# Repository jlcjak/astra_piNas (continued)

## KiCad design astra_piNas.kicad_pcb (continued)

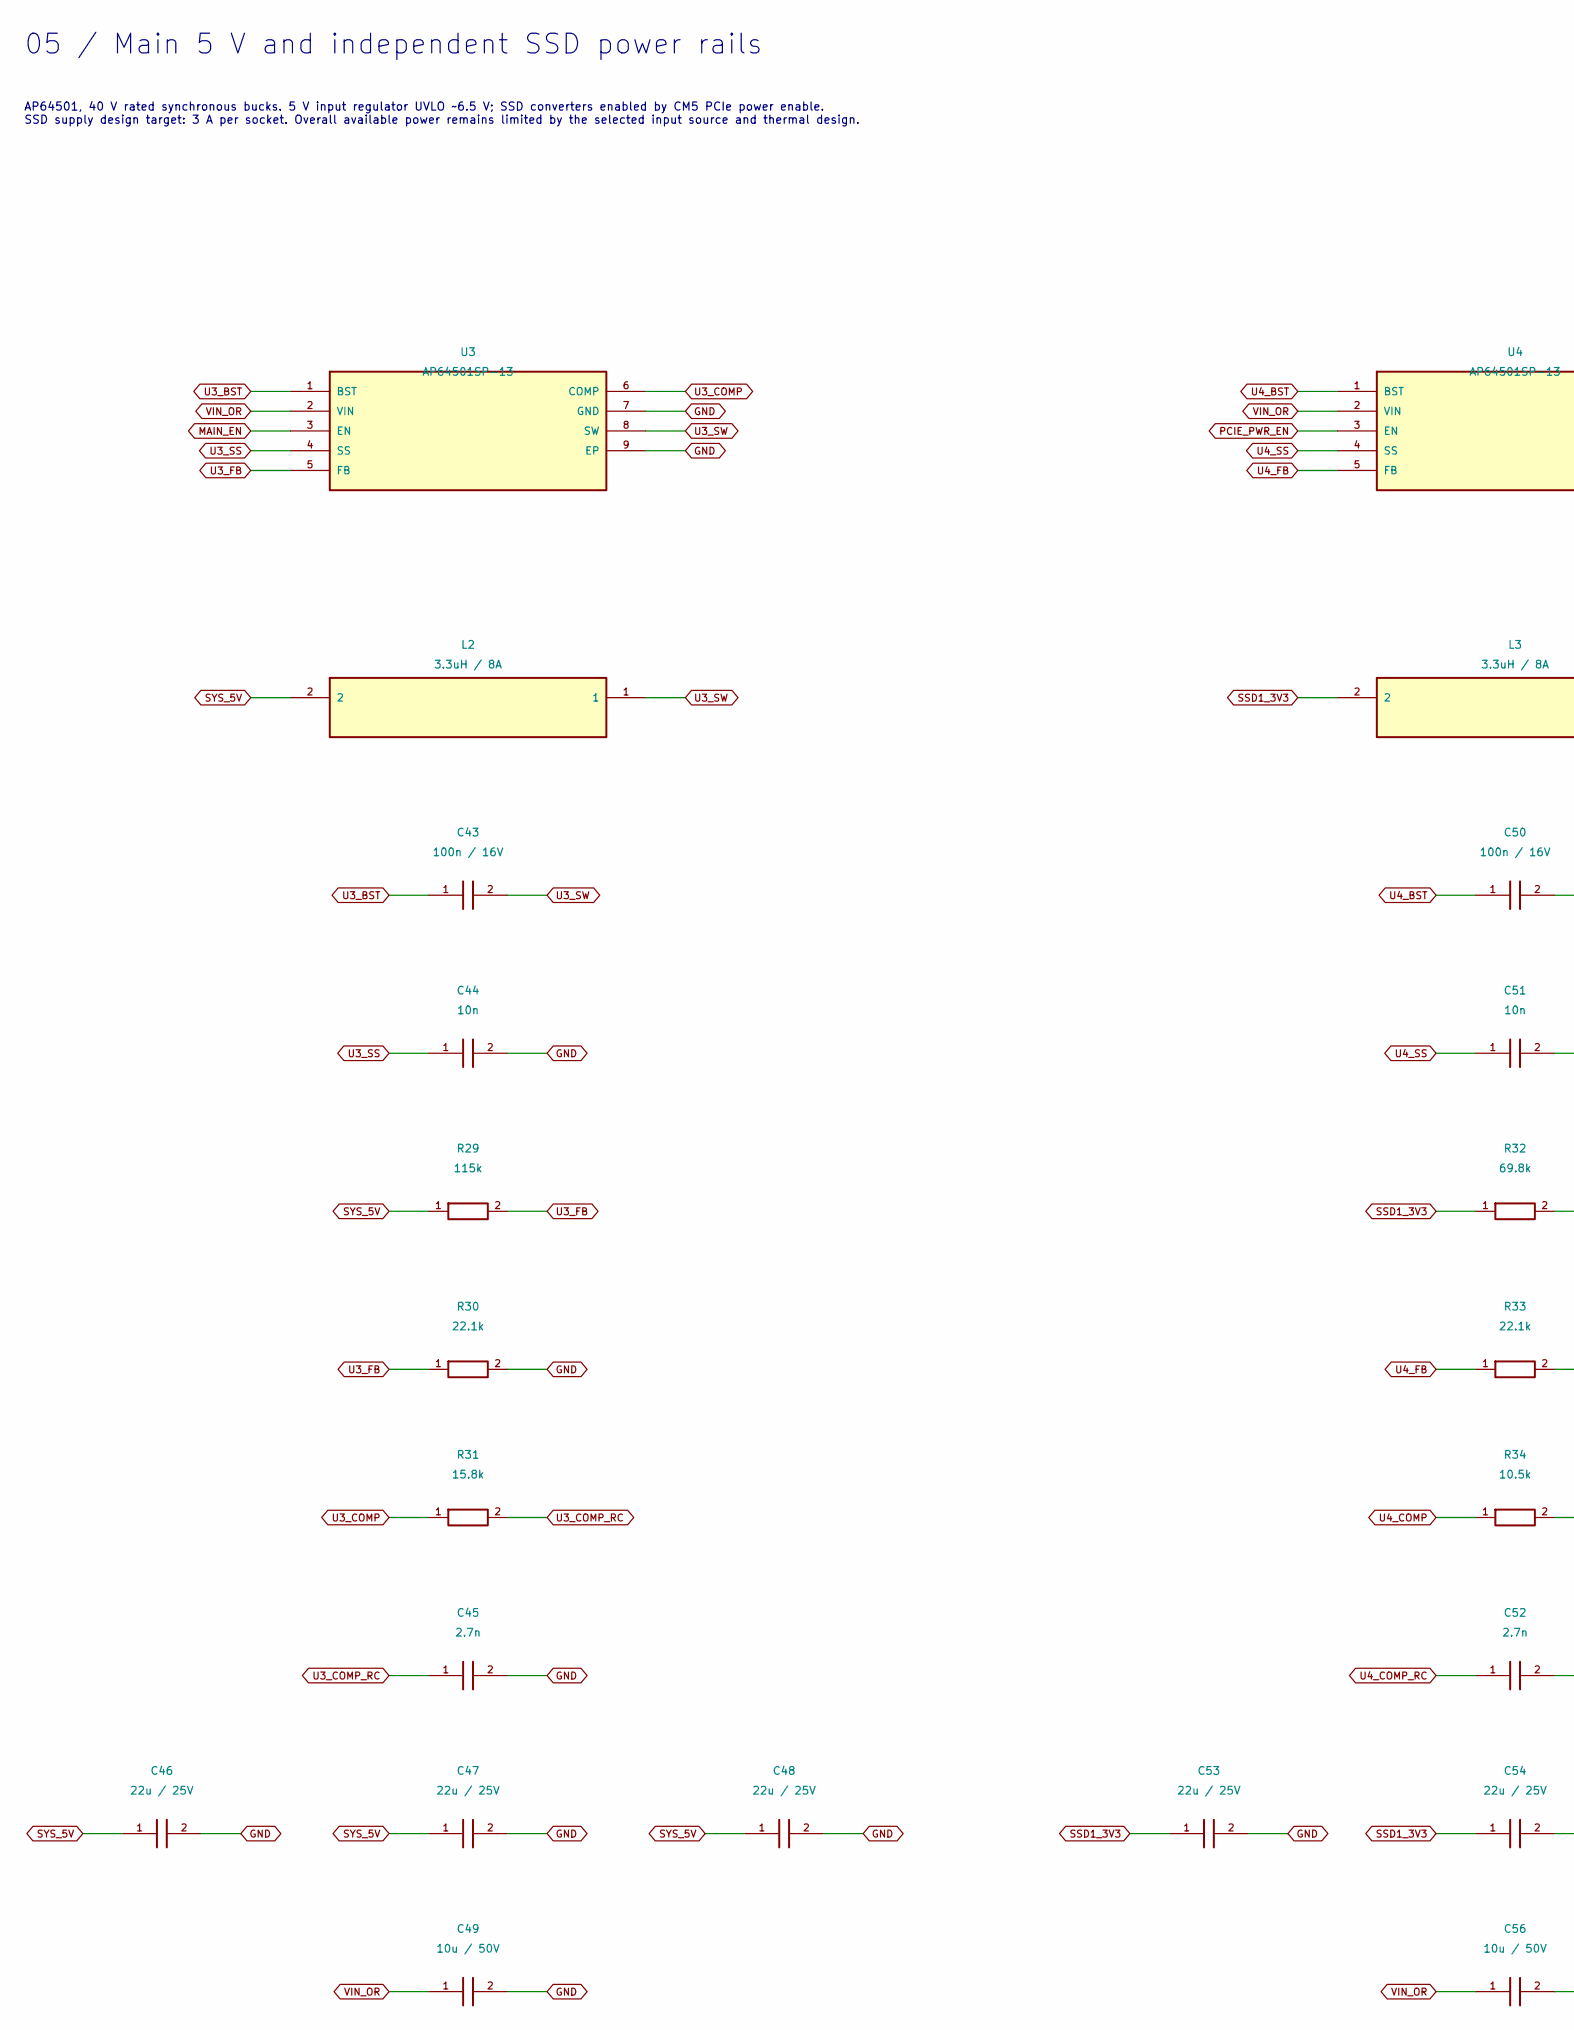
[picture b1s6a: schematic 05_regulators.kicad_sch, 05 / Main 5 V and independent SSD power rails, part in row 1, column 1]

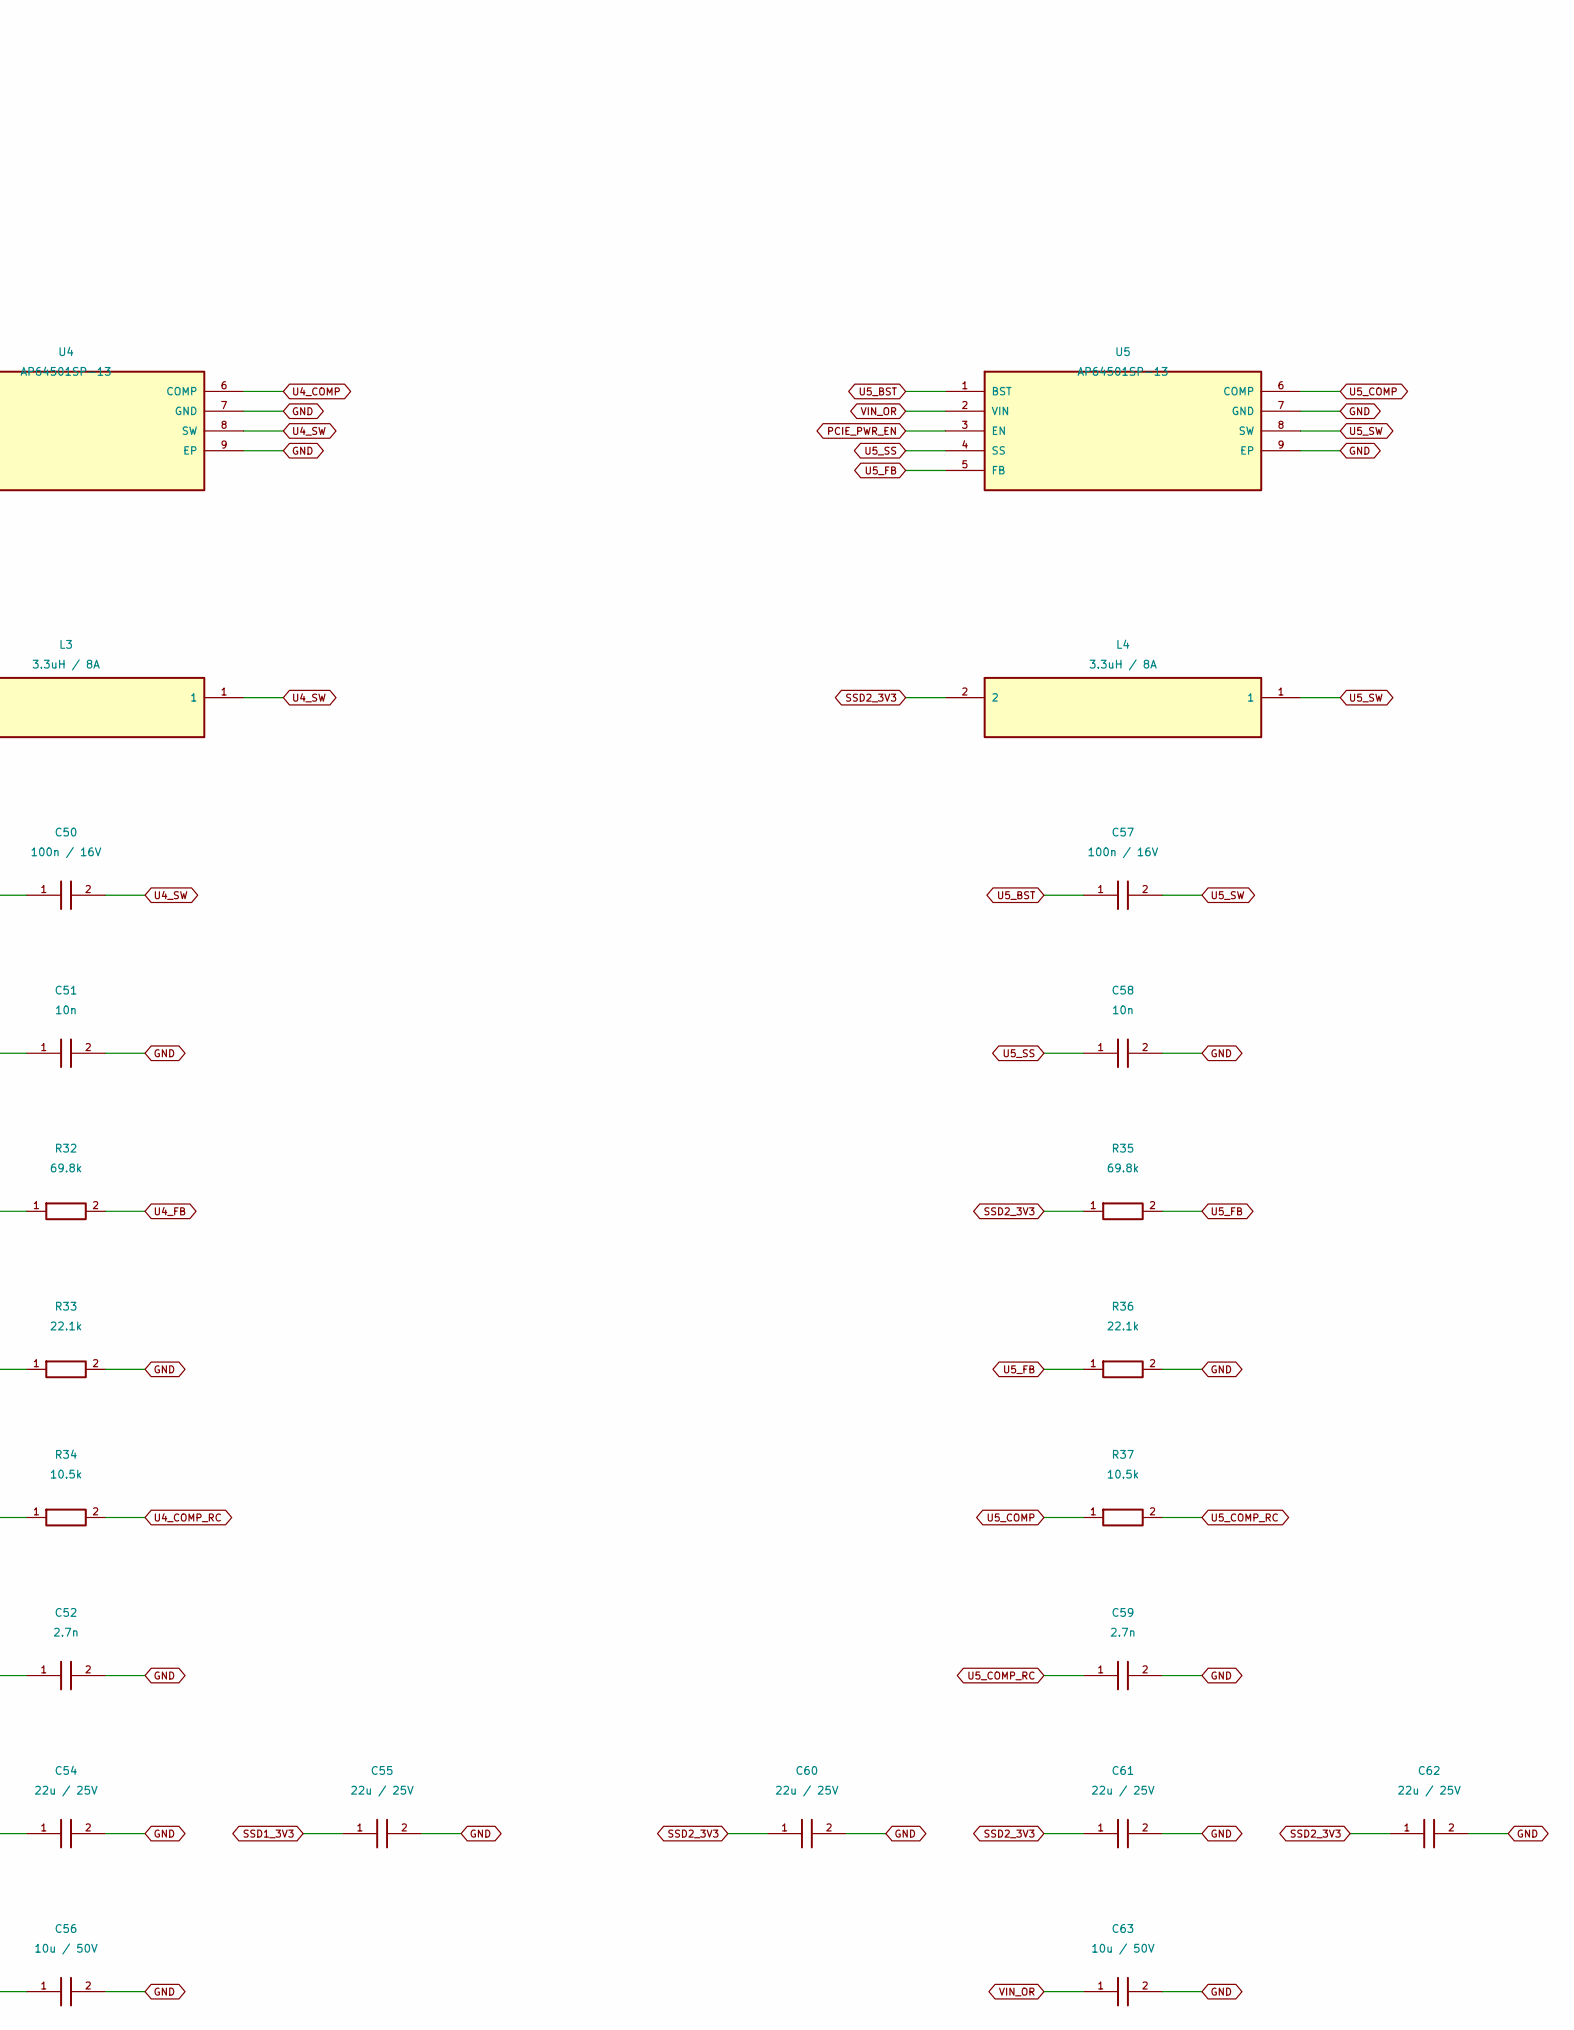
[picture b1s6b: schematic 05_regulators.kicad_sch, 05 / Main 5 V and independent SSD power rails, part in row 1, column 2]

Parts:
C43, C50, C57: 100n / 16V; C_0402_1005Metric; MANUFACTURER PART NUMBER CL05B104KO5NNNC; LCSC Part Number C1525
C44, C51, C58: 10n; C_0603_1608Metric; MANUFACTURER PART NUMBER CL10B103KB8NNNC; LCSC Part Number C1589
C45, C52, C59: 2.7n; C_0603_1608Metric; MANUFACTURER PART NUMBER CL10B272KB8NNNC; LCSC Part Number C84713
C46, C47, C48, C53, C54, C55, C60, C61, C62: 22u / 25V; C_0805_2012Metric; MANUFACTURER PART NUMBER CL21A226MAQNNNE; LCSC Part Number C45783
C49, C56, C63: 10u / 50V; C_1206_3216Metric; MANUFACTURER PART NUMBER CL31B106KAHNNNE; LCSC Part Number C14860
L2, L3, L4: 3.3uH / 8A; IND-SMD_L7.3-W6.6; MANUFACTURER PART NUMBER MDA7050-3R3M; LCSC Part Number C2847540
R29: 115k; R_0603_1608Metric; MANUFACTURER PART NUMBER 0603WAF1153T5E; LCSC Part Number C22783
R30, R33, R36: 22.1k; R_0603_1608Metric; MANUFACTURER PART NUMBER 0603WAF2212T5E; LCSC Part Number C25961
R31: 15.8k; R_0603_1608Metric; MANUFACTURER PART NUMBER 0603WAF1582T5E; LCSC Part Number C22880
R32, R35: 69.8k; R_0603_1608Metric; MANUFACTURER PART NUMBER 0603WAF6982T5E; LCSC Part Number C23098
R34, R37: 10.5k; R_0603_1608Metric; MANUFACTURER PART NUMBER 0603WAF1052T5E; LCSC Part Number C22855
U3, U4, U5: AP64501SP-13; SOIC-8_L4.9-W3.9-P1.27-LS6.0-BL-EP-1; MANUFACTURER PART NUMBER AP64501SP-13; LCSC Part Number C2071517

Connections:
GND: C44.2, C45.2, C46.2, C47.2, C48.2, C49.2, C51.2, C52.2, C53.2, C54.2, C55.2, C56.2, C58.2, C59.2, C60.2, C61.2, C62.2, C63.2, R30.2, R33.2, R36.2, U3.7 (GND), U3.9 (EP), U4.7 (GND), U4.9 (EP), U5.7 (GND), U5.9 (EP); also elsewhere on the board
MAIN_EN: U3.3 (EN); also elsewhere on the board
PCIE_PWR_EN: U4.3 (EN), U5.3 (EN); also elsewhere on the board
SSD1_3V3: C53.1, C54.1, C55.1, L3.2, R32.1; also elsewhere on the board
SSD2_3V3: C60.1, C61.1, C62.1, L4.2, R35.1; also elsewhere on the board
SYS_5V: C46.1, C47.1, C48.1, L2.2, R29.1; also elsewhere on the board
U3_BST: C43.1, U3.1 (BST)
U3_COMP: R31.1, U3.6 (COMP)
U3_COMP_RC: C45.1, R31.2
U3_FB: R29.2, R30.1, U3.5 (FB)
U3_SS: C44.1, U3.4 (SS)
U3_SW: C43.2, L2.1, U3.8 (SW)
U4_BST: C50.1, U4.1 (BST)
U4_COMP: R34.1, U4.6 (COMP)
U4_COMP_RC: C52.1, R34.2
U4_FB: R32.2, R33.1, U4.5 (FB)
U4_SS: C51.1, U4.4 (SS)
U4_SW: C50.2, L3.1, U4.8 (SW)
U5_BST: C57.1, U5.1 (BST)
U5_COMP: R37.1, U5.6 (COMP)
U5_COMP_RC: C59.1, R37.2
U5_FB: R35.2, R36.1, U5.5 (FB)
U5_SS: C58.1, U5.4 (SS)
U5_SW: C57.2, L4.1, U5.8 (SW)
VIN_OR: C49.1, C56.1, C63.1, U3.2 (VIN), U4.2 (VIN), U5.2 (VIN); also elsewhere on the board

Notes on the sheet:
05 / Main 5 V and independent SSD power rails
AP64501, 40 V rated synchronous bucks. 5 V input regulator UVLO ~6.5 V; SSD converters enabled by CM5 PCIe power enable. SSD supply design target: 3 A per socket. Overall available power remains limited by the selected input source and thermal design.

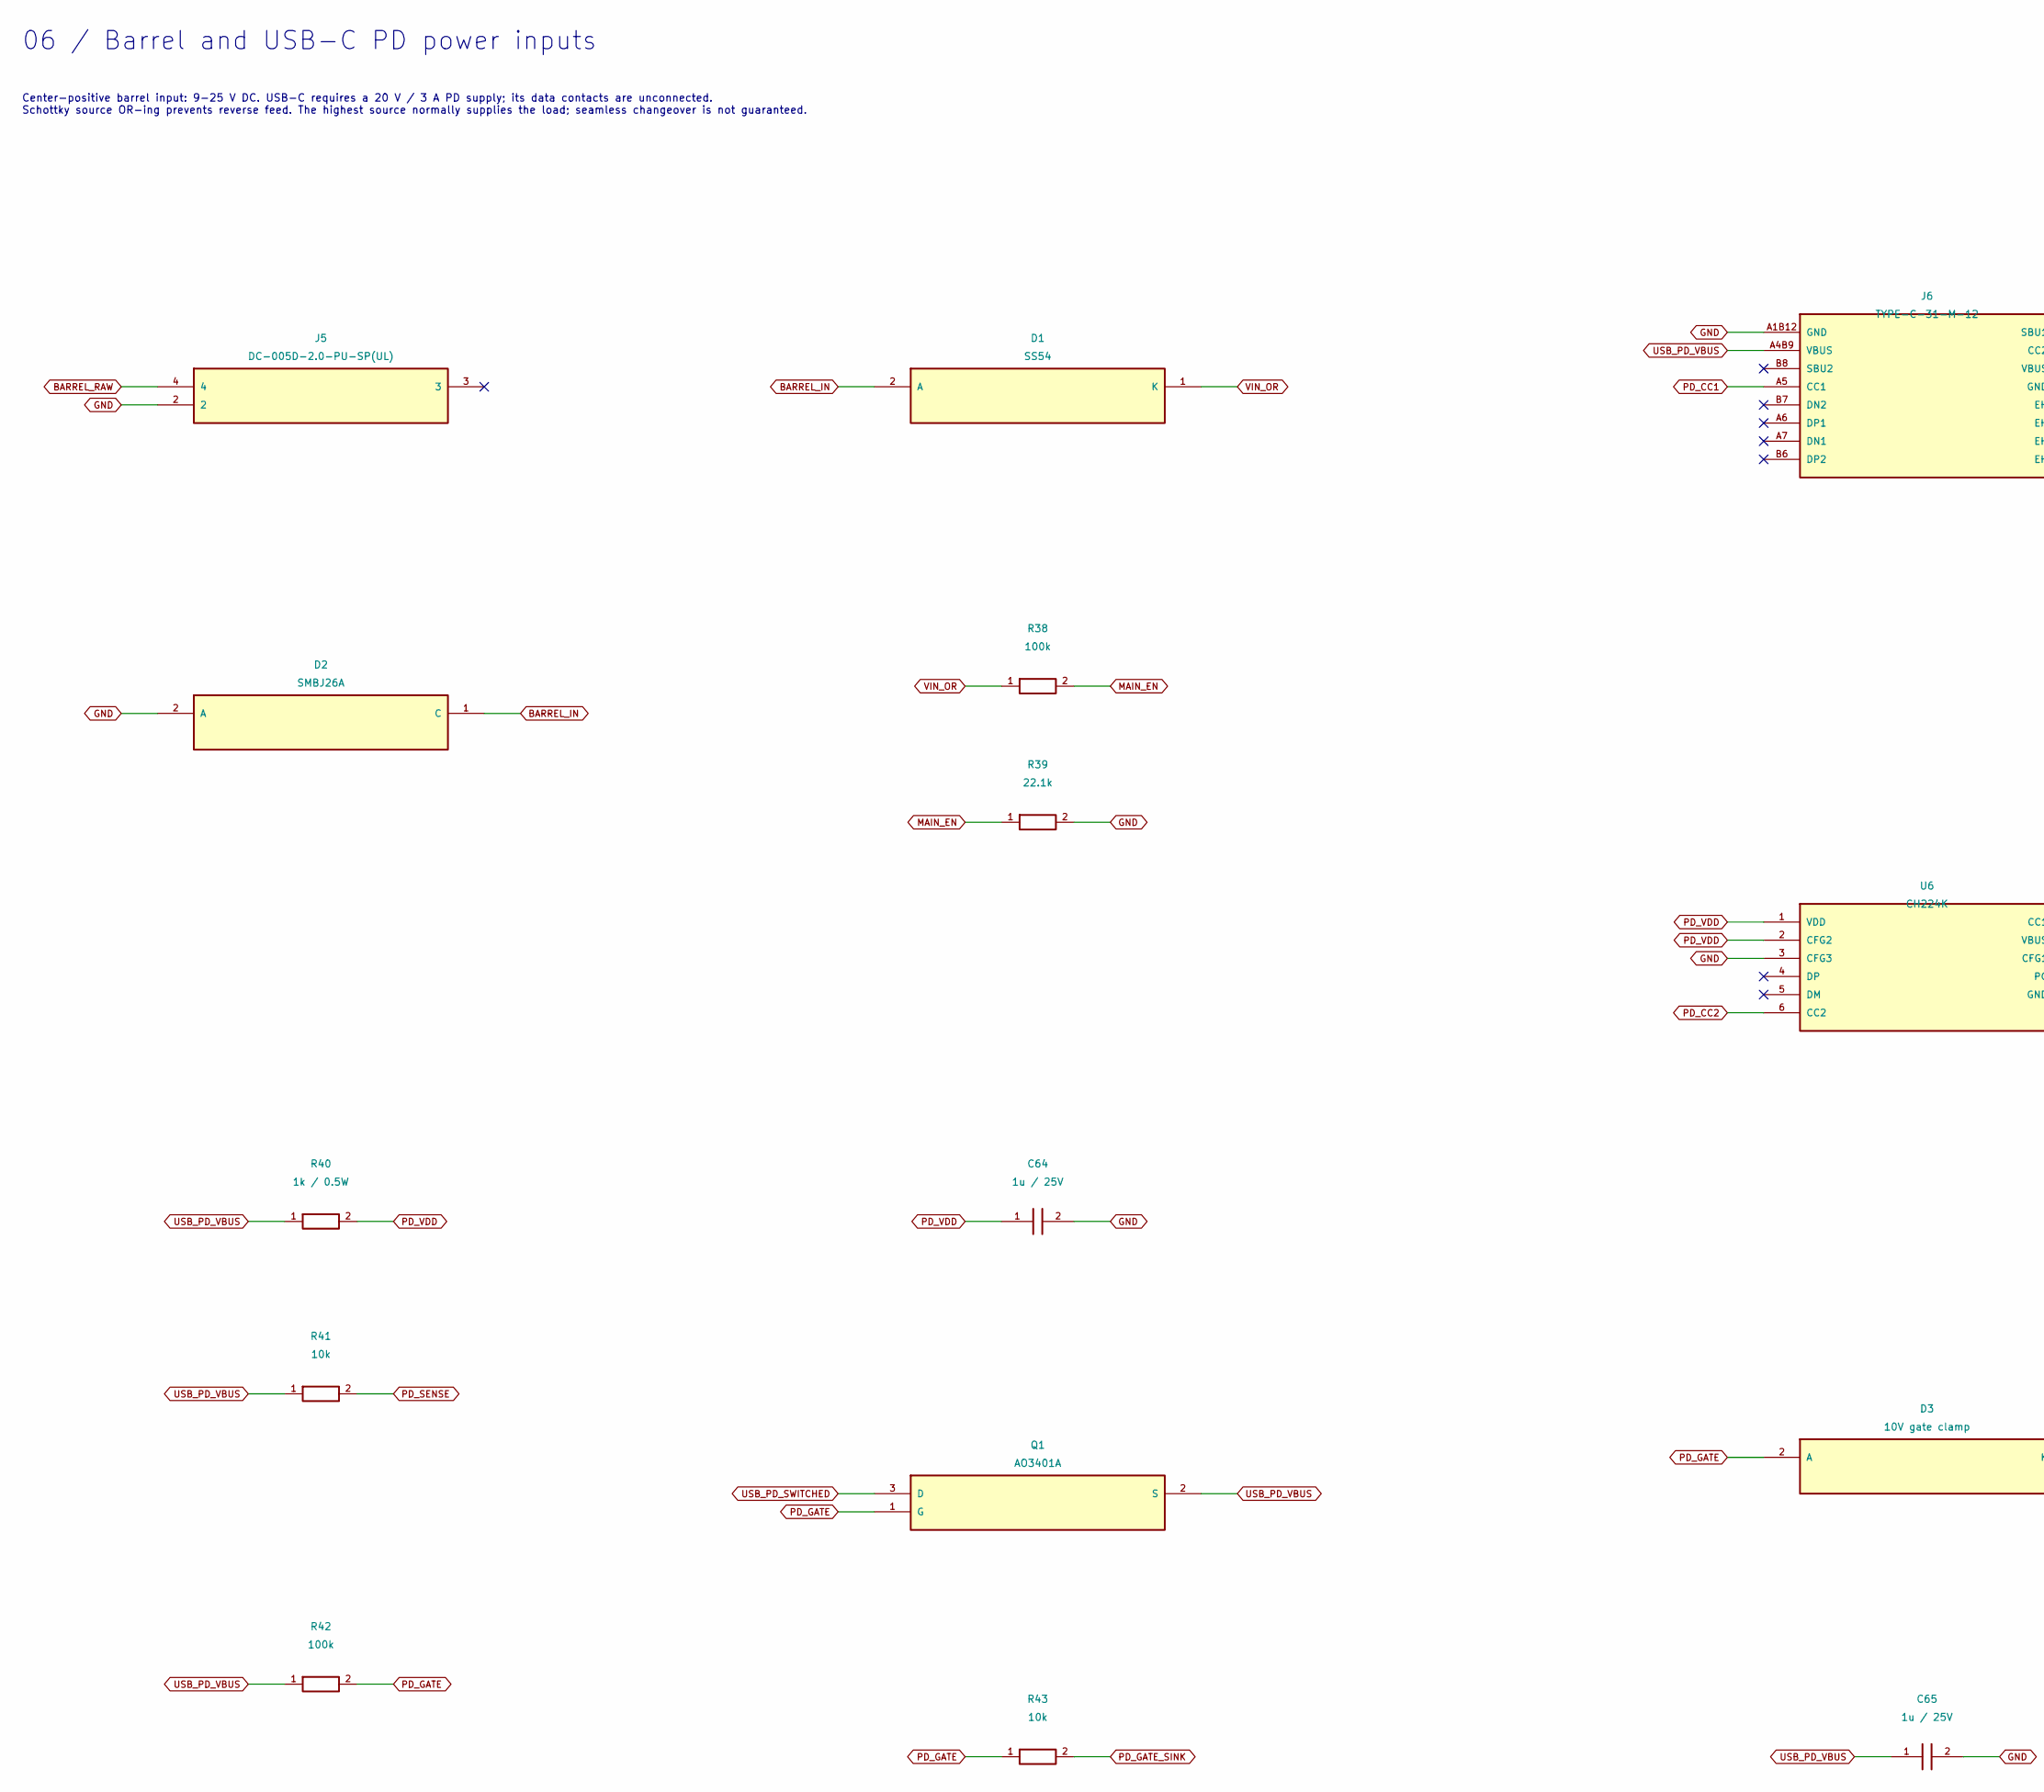
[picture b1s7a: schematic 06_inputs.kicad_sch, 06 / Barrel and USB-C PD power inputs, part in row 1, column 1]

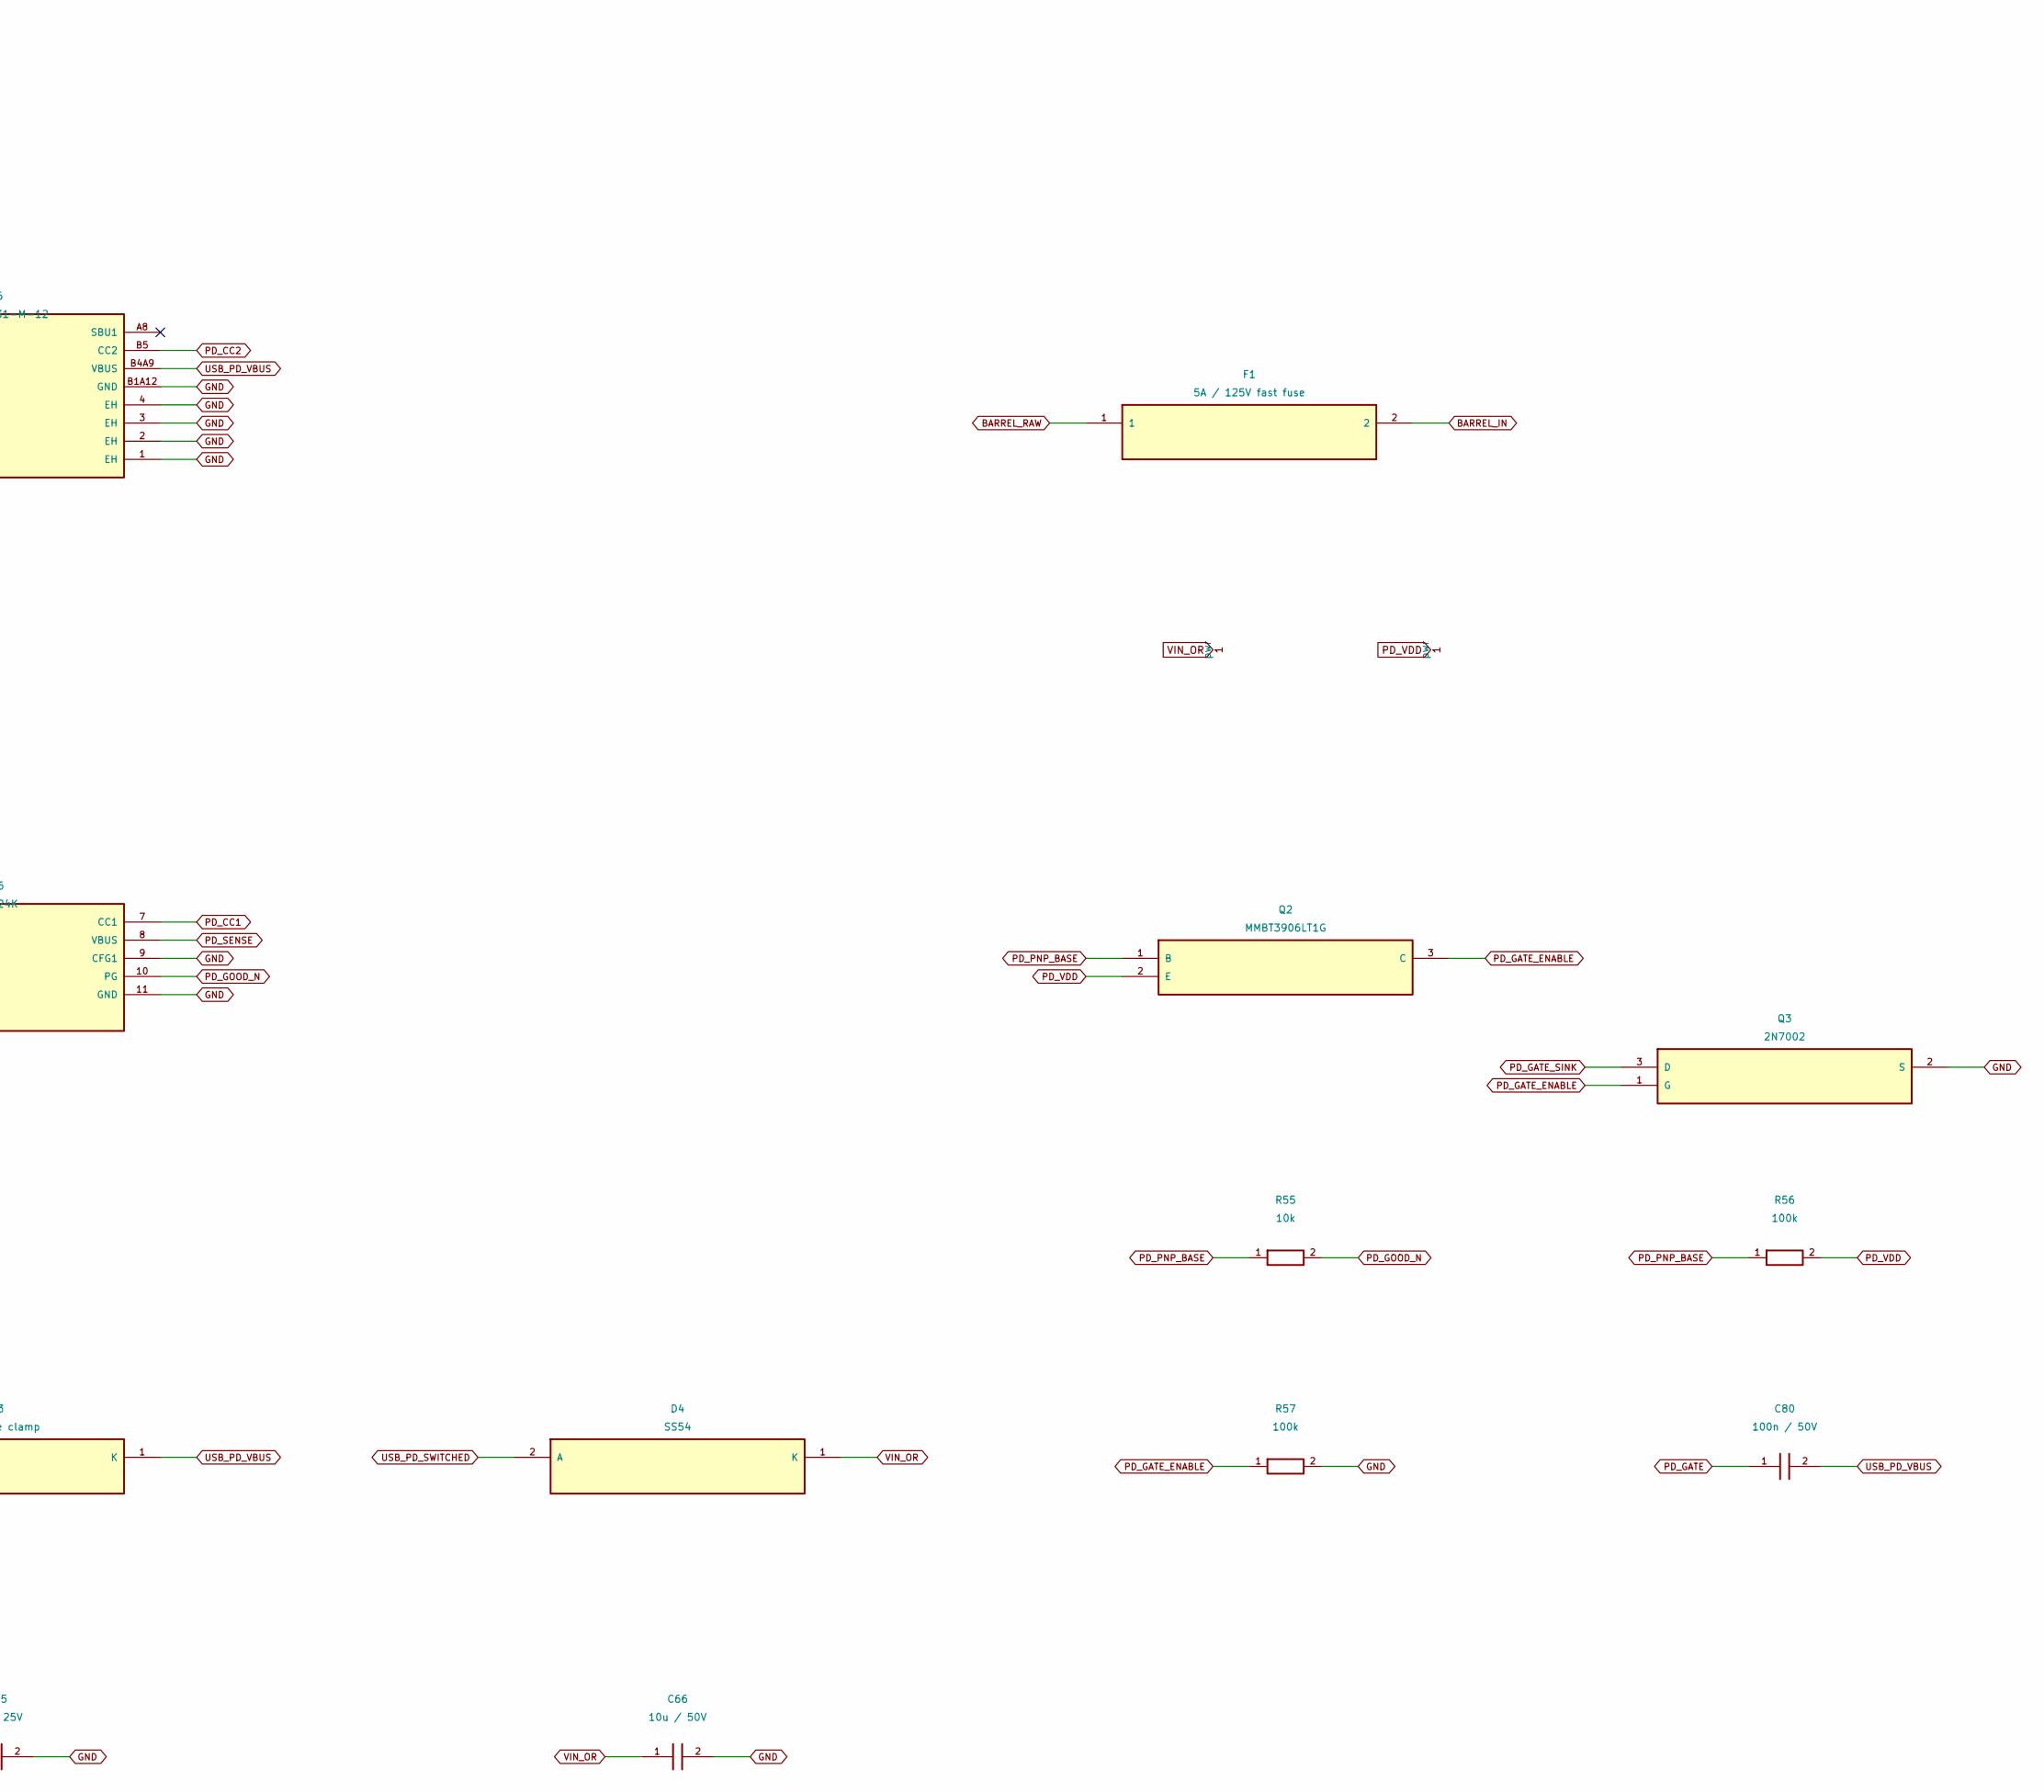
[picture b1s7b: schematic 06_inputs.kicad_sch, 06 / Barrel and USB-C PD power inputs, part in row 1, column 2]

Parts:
C64, C65: 1u / 25V; C_0603_1608Metric; MANUFACTURER PART NUMBER CL10B105KA8NNNC; LCSC Part Number C29936
C66: 10u / 50V; C_1206_3216Metric; MANUFACTURER PART NUMBER CL31B106KAHNNNE; LCSC Part Number C14860
C80: 100n / 50V; C_0603_1608Metric; MANUFACTURER PART NUMBER CL10B104KB8NNNC; LCSC Part Number C1591
D1, D4: SS54; SMA_L4.4-W2.8-LS5.4-RD; MANUFACTURER PART NUMBER SS54; LCSC Part Number C123946
D2: SMBJ26A; SMB_L4.6-W3.6-LS5.3-RD; MANUFACTURER PART NUMBER SMBJ26A; LCSC Part Number C123820
D3: 10V gate clamp; SOD-123_L2.8-W1.8-LS3.7-RD; MANUFACTURER PART NUMBER BZT52C10; LCSC Part Number C2103
F1: 5A / 125V fast fuse; FUSE-SMD_L6.1-W2.6; MANUFACTURER PART NUMBER 0451005.MRL; LCSC Part Number C48467
J5: DC-005D-2.0-PU-SP(UL); DC-IN-TH_DC-005D-2.0-PU-SP; MANUFACTURER PART NUMBER DC-005D-2.0-PU-SP(UL); LCSC Part Number C7428653
J6: TYPE-C-31-M-12; USB-C_SMD-TYPE-C-31-M-12_1; MANUFACTURER PART NUMBER TYPE-C-31-M-12; LCSC Part Number C165948
Q1: AO3401A; SOT-23_L2.9-W1.3-P1.90-LS2.4-BR; MANUFACTURER PART NUMBER AO3401A; LCSC Part Number C15127
Q2: MMBT3906LT1G; SOT-23-3_L2.9-W1.3-P1.90-LS2.4-BR; MANUFACTURER PART NUMBER MMBT3906LT1G; LCSC Part Number C53444
Q3: 2N7002; SOT-23-3_L2.9-W1.3-P1.90-LS2.4-BR; MANUFACTURER PART NUMBER 2N7002; LCSC Part Number C8545
R38, R42, R56, R57: 100k; R_0603_1608Metric; MANUFACTURER PART NUMBER 0603WAF1003T5E; LCSC Part Number C25803
R39: 22.1k; R_0603_1608Metric; MANUFACTURER PART NUMBER 0603WAF2212T5E; LCSC Part Number C25961
R40: 1k / 0.5W; R_1206_3216Metric; MANUFACTURER PART NUMBER ESR18EZPF1001; LCSC Part Number C2074262
R41, R43, R55: 10k; R_0603_1608Metric; MANUFACTURER PART NUMBER RC0603FR-0710KL; LCSC Part Number C98220
U6: CH224K; ESSOP-10_L4.9-W3.9-P1.0-LS6.0-TL-EP; MANUFACTURER PART NUMBER CH224K; LCSC Part Number C970725

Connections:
BARREL_IN: D1.2 (A), D2.1 (C), F1.2
BARREL_RAW: F1.1, J5.4
GND: C64.2, C65.2, C66.2, D2.2 (A), J5.2, J6.1 (EH), J6.2 (EH), J6.3 (EH), J6.4 (EH), J6.A1B12 (GND), J6.B1A12 (GND), Q3.2 (S), R39.2, R57.2, U6.3 (CFG3), U6.9 (CFG1), U6.11 (GND); also elsewhere on the board
MAIN_EN: R38.2, R39.1; also elsewhere on the board
PD_CC1: J6.A5 (CC1), U6.7 (CC1)
PD_CC2: J6.B5 (CC2), U6.6 (CC2)
PD_GATE: C80.1, D3.2 (A), Q1.1 (G), R42.2, R43.1
PD_GATE_ENABLE: Q2.3 (C), Q3.1 (G), R57.1
PD_GATE_SINK: Q3.3 (D), R43.2
PD_GOOD_N: R55.2, U6.10 (PG)
PD_PNP_BASE: Q2.1 (B), R55.1, R56.1
PD_SENSE: R41.2, U6.8 (VBUS)
PD_VDD: C64.1, Q2.2 (E), R40.2, R56.2, U6.1 (VDD), U6.2 (CFG2)
USB_PD_SWITCHED: D4.2 (A), Q1.3 (D)
USB_PD_VBUS: C65.1, C80.2, D3.1 (K), J6.A4B9 (VBUS), J6.B4A9 (VBUS), Q1.2 (S), R40.1, R41.1, R42.1
VIN_OR: C66.1, D1.1 (K), D4.1 (K), R38.1; also elsewhere on the board

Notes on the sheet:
06 / Barrel and USB-C PD power inputs
Center-positive barrel input: 9-25 V DC. USB-C requires a 20 V / 3 A PD supply; its data contacts are unconnected. Schottky source OR-ing prevents reverse feed. The highest source normally supplies the load; seamless changeover is not guaranteed.
